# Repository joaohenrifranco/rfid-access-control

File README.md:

_Note: this repo is not being actively maintained_
# RFID Access Control
Access control system developed to log each entrance and exit of internal rooms at a lab located at Federal University of Rio de Janeiro (UFRJ).

## Server
Django based server that provides a RESTful API for authentication and logging. Also provides a control panel made with Django Admin.

Code and more detailed info inside `server/`
## Client
Developed and tested for Arduino Mega using [PlatformIO](https://platformio.org/).

Works primarily with RFID readers, one for outside and one for inside, checking if the read UID is registered in server database and has sufficient privileges for unlocking the desired room.

Password authentication is optional through a 4x3 matrix keyboard, providing some kind of security.

Code and more detailed info inside `client/`

## Extras

### Front door "smart doorbell"
Developed in parallel with this project. Works with a RaspberryPi 3 located at the front door and a VoIP server (Asterisk) for live video transferring.

When doorbell is rang, the raspberry calls all people inside the lab, with some preconfigured order. They can take the call, check the camera and open the door if desired. All with their smartphone, PC or any other SIP-capable device.

Employees can automatically get in with their RFID tags registered in this system.

Also, everything is logged through this API.

For code and more info on that check the repositories below:

 - [Asterisk server](https://github.com/joaohenriquef/asterisk-smartdoor)
 - [Raspberry client](https://github.com/joaohenriquef/rasp-smartdoor)

## Disclaimer

Note that it is not made with security in mind and its main purpouse is internal logging, therefore it may be vulnerable to external attackers.

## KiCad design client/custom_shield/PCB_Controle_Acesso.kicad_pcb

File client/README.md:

# Client

## Disclaimer
Every instruction shown below is only valid for this single project. Any changes on code, hardware or others may cause malfunctions or adding other requirements.

## Hardware requirements
For a single Arduino client you will need:
* 1x Arduino MEGA 2560;
* 1x Ethernet Shield W5100 (for communicating with server);
* 2x RFID Reader MFRC-522 (for reading UIDs);
* 2x RGB LED;
* 1x 5V active buzzer;
* 1x TCRT5000 optical sensor (for checking if the door is closed or not);
* 1x LM2596 DC/DC converter (for supplying Arduino through a 12V power source);
* 1x MOSFET IRF540N (for unlocking the door);
* 3x 150Ω resistors (for RED pins on LEDs and infra-red LED);
* 2x 220Ω resistors (for GREEN pins on LEDs);
* 2x 470Ω resistors (for BLUE pins on LEDs);
* 1x 10KΩ resistor (for LDR);
* 1x 4x3 matrix keypad (optional);
* 1x Custom shield*

*For further information on this, check the [Custom shield](#custom-shield) section on this file.

## Implementation
A single client consists on two "blocks" of equipment. One block inside the room and, the other, outside, as shown below:

## Algorithm
The Arduino code is pretty simple and works as the diagram below:
* Setup:

* Loop:

## Custom shield
In order to ease implementation, a custom PCB was designed with [KiCad](http://kicad-pcb.org/), in the shape of an Arduino Mega Shield. The electrical schematic is the following and all the files related to the PCB design may be found inside `custom_shield/`:

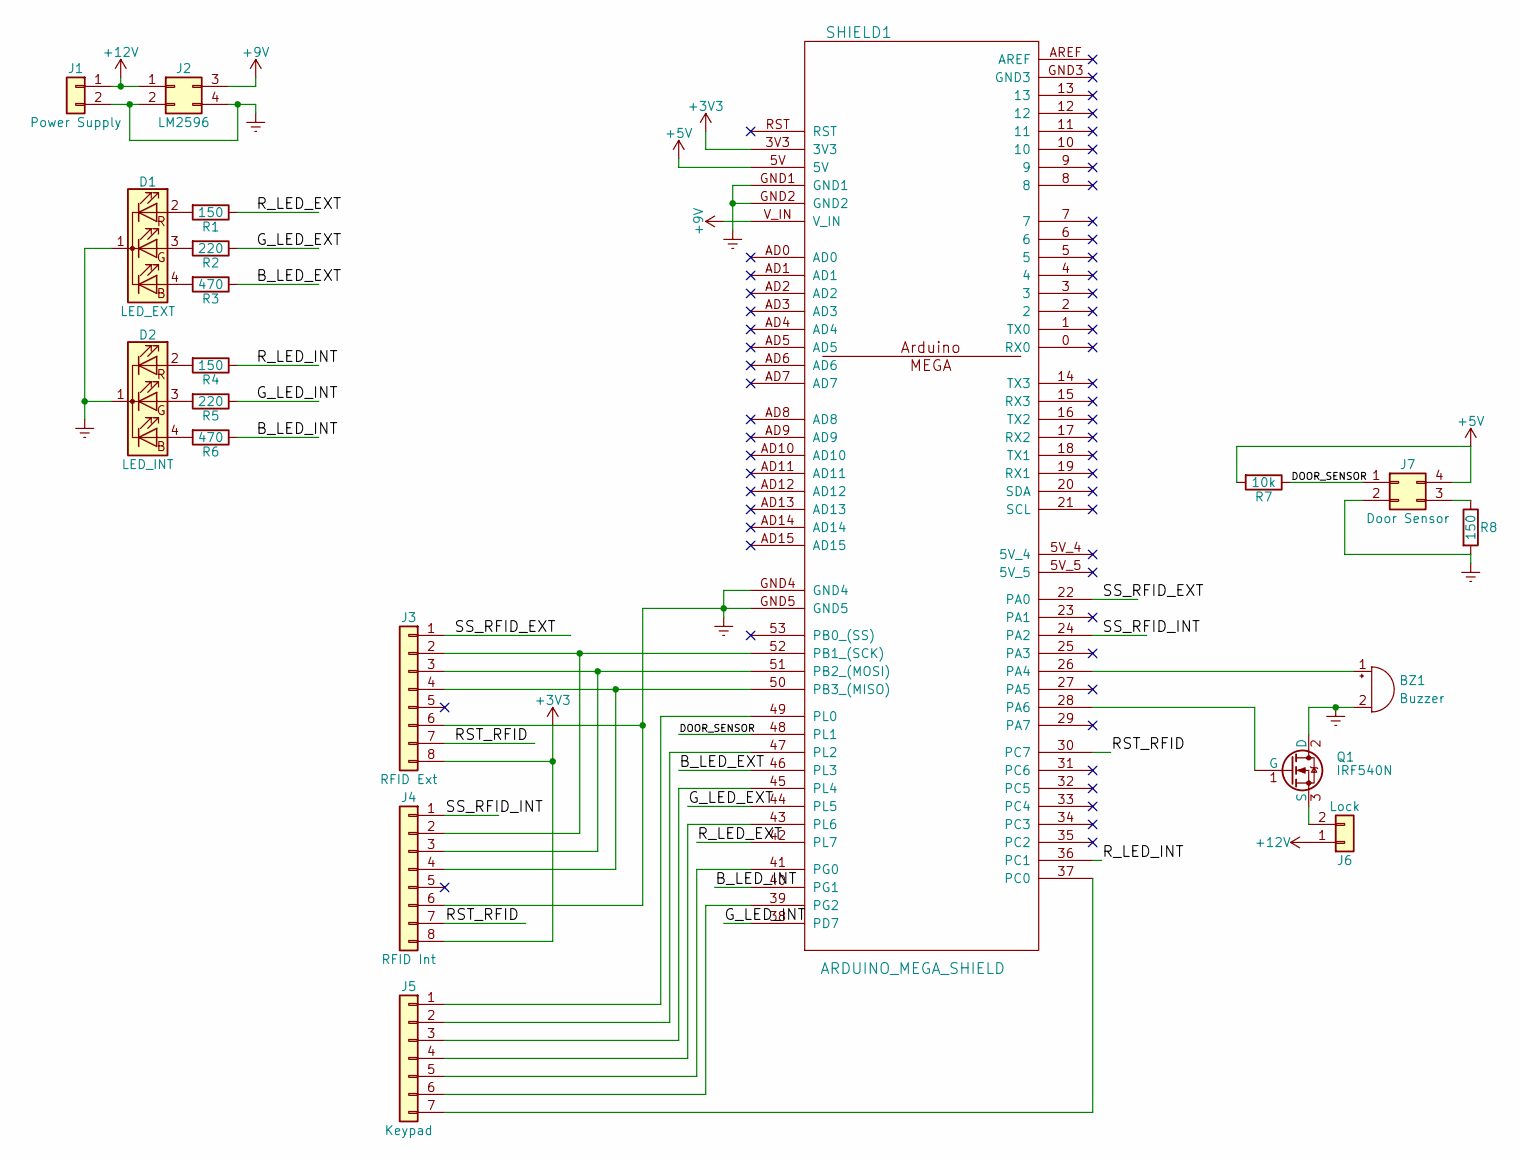
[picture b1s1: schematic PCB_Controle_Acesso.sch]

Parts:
BZ1: Buzzer; Buzzer_12x9.5RM7.6
D1: LED_EXT; Pin_Header_Straight_1x04_Pitch2.54mm
D2: LED_INT; LED_D5.0mm-4
J1: Power Supply; TerminalBlock_Phoenix_MKDS1.5-2pol
J2: LM2596; lm2596
J3: RFID Ext; Pin_Header_Straight_1x08_Pitch2.54mm
J4: RFID Int; RFID-RC522
J5: Keypad; Pin_Header_Straight_1x07_Pitch2.54mm
J6: Lock; TerminalBlock_Phoenix_MKDS1.5-2pol
J7: Door Sensor; Pin_Header_Straight_2x02_Pitch2.54mm
Q1: IRF540N; TO-220-3_Horizontal
R1, R4, R8: 150; R_Axial_DIN0204_L3.6mm_D1.6mm_P7.62mm_Horizontal
R2, R5: 220; R_Axial_DIN0204_L3.6mm_D1.6mm_P7.62mm_Horizontal
R3, R6: 470; R_Axial_DIN0204_L3.6mm_D1.6mm_P7.62mm_Horizontal
R7: 10k; R_Axial_DIN0204_L3.6mm_D1.6mm_P7.62mm_Horizontal
SHIELD1: ARDUINO_MEGA_SHIELD; ARDUINO_MEGA_SHIELD_ETH_MODIFIED

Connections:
+5V: J7.4, R7.2, SHIELD1.5V
+9V: J2.3, SHIELD1.V_IN
+12V: J1.1, J2.1, J6.1
/B_LED_EXT: R3.1, SHIELD1.46 (PL3)
/B_LED_INT: R6.1, SHIELD1.40 (PG1)
/DOOR_SENSOR: J7.1, R7.1, SHIELD1.48 (PL1)
/G_LED_EXT: R2.1, SHIELD1.44 (PL5)
/G_LED_INT: R5.1, SHIELD1.38 (PD7)
/RST_RFID: J3.7, J4.7, SHIELD1.30 (PC7)
/R_LED_EXT: R1.1, SHIELD1.42 (PL7)
/R_LED_INT: R4.1, SHIELD1.36 (PC1)
/SS_RFID_EXT: J3.1, SHIELD1.22 (PA0)
/SS_RFID_INT: J4.1, SHIELD1.24 (PA2)
unnamed: BZ1.1 (-), SHIELD1.26 (PA4)
unnamed: D1.2 (RA), R1.2
unnamed: D1.3 (GA), R2.2
unnamed: D1.4 (BA), R3.2
unnamed: D2.2 (RA), R4.2
unnamed: D2.3 (GA), R5.2
unnamed: D2.4 (BA), R6.2
unnamed: J3.2, J4.2, SHIELD1.52 (PB1_(SCK))
unnamed: J3.3, J4.3, SHIELD1.51 (PB2_(MOSI))
unnamed: J3.4, J4.4, SHIELD1.50 (PB3_(MISO))
unnamed: J5.1, SHIELD1.49 (PL0)
unnamed: J5.2, SHIELD1.47 (PL2)
unnamed: J5.3, SHIELD1.45 (PL4)
unnamed: J5.4, SHIELD1.43 (PL6)
unnamed: J5.5, SHIELD1.41 (PG0)
unnamed: J5.6, SHIELD1.39 (PG2)
unnamed: J5.7, SHIELD1.37 (PC0)
unnamed: J6.2, Q1.3 (S)
unnamed: J7.3, R8.1
unnamed: Q1.1 (G), SHIELD1.28 (PA6)

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
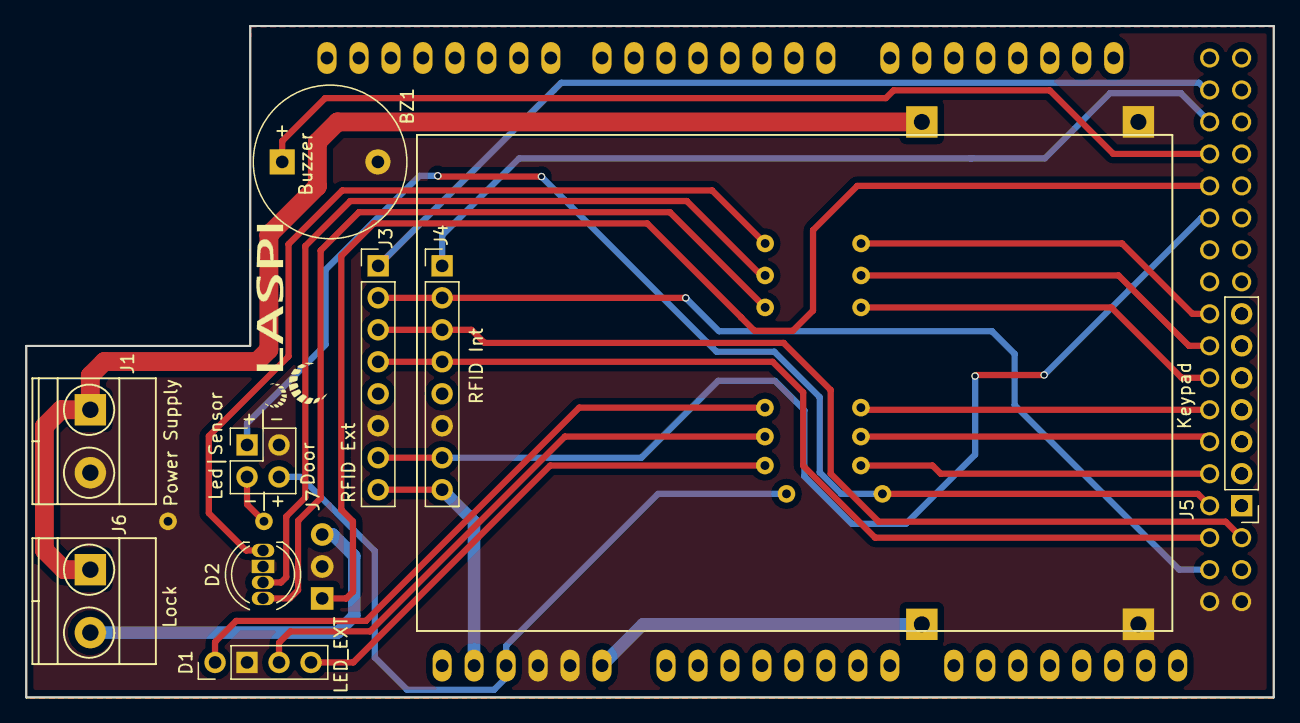
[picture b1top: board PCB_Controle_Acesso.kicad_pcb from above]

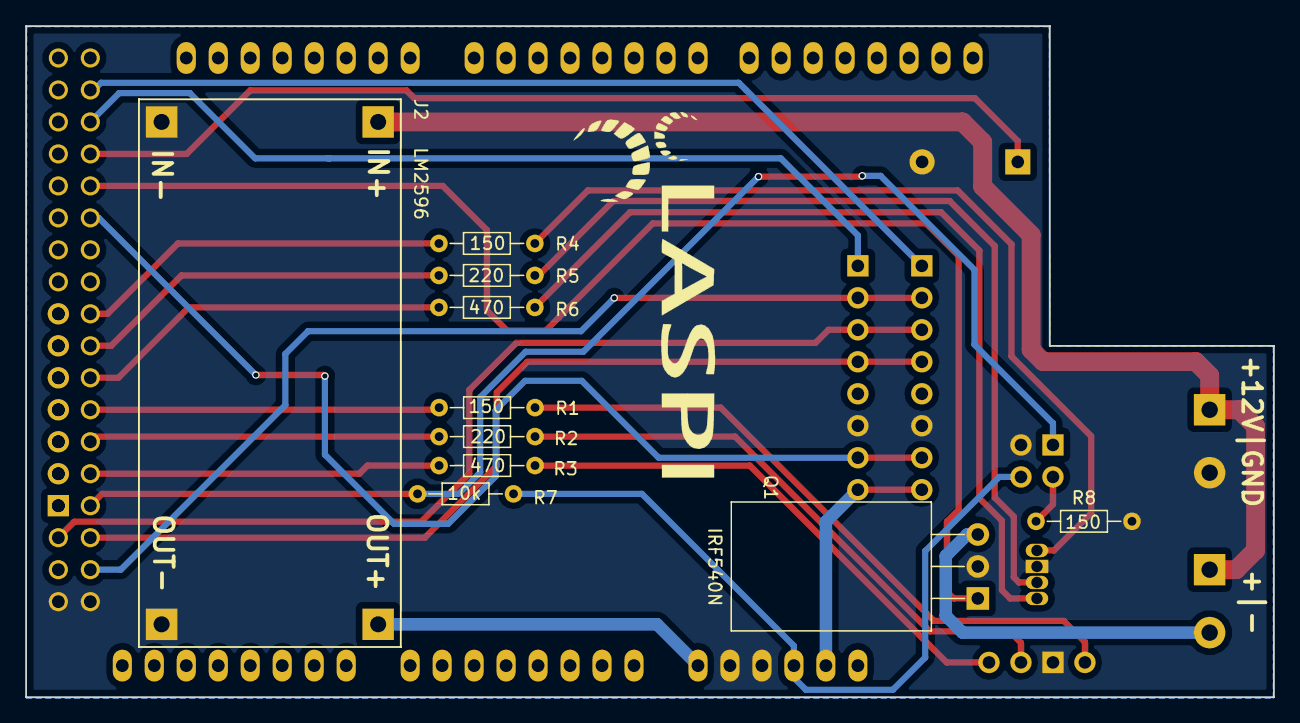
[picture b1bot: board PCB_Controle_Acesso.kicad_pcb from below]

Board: 2 copper layers, 99.1 x 53.3 mm, 20 parts (10 on the bottom side), 35 nets.

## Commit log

2018-01-24 Initial client commit
2018-01-24 Server initial commit
2018-01-24 Initial main code
2018-01-25 Added a procedure for RGB LED
2018-01-25 Create server
2018-01-25 Added infrastracture for ethernet client
2018-01-25 Make server respond to requests
2018-01-25 Added function to get password from keypad
2018-01-25 Added hash function (SHA-1)
2018-01-25 Added first implementation of POST request
2018-01-25 Create sql file for initial db setup
2018-01-25 Disable unused django apps
2018-01-25 Made modifications on the JSON request model
2018-01-25 Add client-server schematic image
2018-01-25 Add flowchart to README.md
2018-01-31 Remove database SQL
2018-01-31 Add .gitignore
2018-01-31 Add testing code snippet to loop
2018-01-31 Create model
2018-01-31 Recreate clean server project
2018-02-01 Syntax correction in models.py
2018-02-01 Show all fields in django admin
2018-02-01 Treat post requests
2018-02-07 Added SHA-256 hash function and testing code block
2018-02-07 Changed RFID module function and added the full workflow code for the client
2018-02-21 Update request response flowchart
2018-02-21 Add correct api for auth visitor
2018-02-21 Fix various syntax errors
2018-02-21 Make model attributes Integer when needed
2018-02-21 Changed request data format
2018-02-22 Added visitor card identification flow to chart
2018-02-22 Add VISITOR_RFID_FOUND label
2018-02-22 Correct json parser, New file for error codes, Fix visitor logic
2018-02-22 Add migrations folder to .gitignote
2018-02-22 Fix syntax error
2018-02-22 Initial log implementation
2018-02-22 Added DEV02 IP Address in ALLOWED_HOSTS
2018-02-22 Added laspi-icp to ALLOWED_HOSTS
2018-02-22 Error codes tweak
2018-02-22 Fixed hashed password size to SHA256
2018-02-22 Add test host
2018-02-22 (Re) Fixed status codes
2018-02-22 Fully functional first version of client (visitors not included)
2018-02-22 Improve logging
2018-02-26 Add logging error
2018-02-26 Add new errors to model
2018-02-26 Fixed all logging at request_unlock
2018-02-26 Add test database upload
2018-02-26 Remove debug prints
2018-02-26 Fix malformed POST exception response
2018-02-26 Add api module to logging
2018-02-26 Log at auth api
2018-03-01 Added OpenedDoor and Buzzer funcions
2018-03-01 Complete visitor auth
2018-03-07 Changed LED blinking procedure
2018-03-07 Migrated to Arduino Mini Pro 5V/16MHz
2018-03-07 FIxed "BlinkRGB" not declared issue
2018-03-08 Code adapted for Arduino Pro Mini (issues w/ Ethernet)
2018-03-09 Set greater upload speed
2018-03-09 Partial fix for arduino mini
2018-03-09 Add customizations to admin page
2018-03-09 Remove unused commented code
2018-03-09 Add password field to User
2018-03-12 Refactor server directory structure
2018-03-12 Refactor api app name
2018-03-19 Remove migrations from git
2018-03-19 Implement partial user form with password
2018-03-19 Implement custom hash (SHA256)
2018-03-19 Fix user creation page
2018-03-19 Add .sqlite3 files and migrations to list
2018-03-20 Make Event read-only at admin page
2018-03-21 Adapted code to Arduino MEGA 2560
2018-03-21 Fix auth api to work with hashed passwords
2018-03-21 Remove already done TODO comment
2018-03-28 Partial many to many user-card implementation
2018-03-28 Update model
2018-03-29 Fix many-to-many user-card implementation
2018-03-29 Cosmetic changes
2018-03-29 Double association partial fix
2018-04-02 Refactor api module to accesscontrol
2018-04-04 Disable consistency check to make server usable
2018-04-06 Set debug flag to false and make correct ajustments
2018-04-06 Add PT-BR translations
2018-04-06 Add .po locale files
2018-04-06 Add locale related stuff
2018-04-09 Updated function GenerateVisitorPostData
2018-04-16 Made changes for visitor supporting
2018-04-16 Fixed minor issues
2018-04-16 Fix missing import
2018-04-19 Refactor errors as consts
2018-04-19 Add front door integration
2018-05-16 Changed var names for better understanding and implemented UnlockDoor
2018-05-16 Granted Level 2 and 3 access for employees
2018-05-16 Fix system crashing bugs
2018-05-16 Allow any host running the server
2018-05-16 Fix admin event page crash
2018-05-16 Variable name refactoring
2018-05-16 Fix minor error after refactoring
2018-05-16 Fix wrong password log
2018-05-16 Remove compiled messages
2018-05-16 Ajust event visualization
2018-05-17 Minor code rewriting
2018-05-17 Make translations work
2018-05-18 Visitors fully working
2018-05-18 Implemented timeouts
2018-05-18 Set password as optional field
2018-05-18 Fix authenticated log
2018-05-18 Prepare code for pre_save procedure
2018-05-21 Make title translatable
2018-05-21 Make tag association verification, plural translations fixed
2018-05-21 Cosmetic code changes
2018-05-21 Cosmetic changes, tag record deletion prevention
2018-05-21 Better translations
2018-05-21 Fix timezone warning
2018-06-19 Make RFID query case insensitive
2018-06-19 Remove incorrect max lenght from uid field
2018-06-19 Add max_lenght attribute of 256
2018-06-26 Updated code delays
2018-07-04 Disable CSRF verification at front door unlock api
2018-07-04 Remove incorrect 'unique' constraint for event sip
2018-07-10 Fixed issues with posting
2018-07-10 Fix capitalization at Admin Page
2018-07-10 Fix GET response from API
2018-07-12 Solved minor security issues
2018-07-12 Uploaded client README file
2018-07-12 Minor update on client README file
2018-07-12 Updated client README
2018-07-12 Fixed filename issues
2018-07-27 Tried to fix minor issues w/ response time
2018-07-27 Fixed issues
2018-08-01 Final version
2018-08-01 Minor changes
2018-08-01 Fixed memory leak
